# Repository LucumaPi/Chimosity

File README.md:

# Chimosity
Sobre el auto robótico con Jhonny Five.

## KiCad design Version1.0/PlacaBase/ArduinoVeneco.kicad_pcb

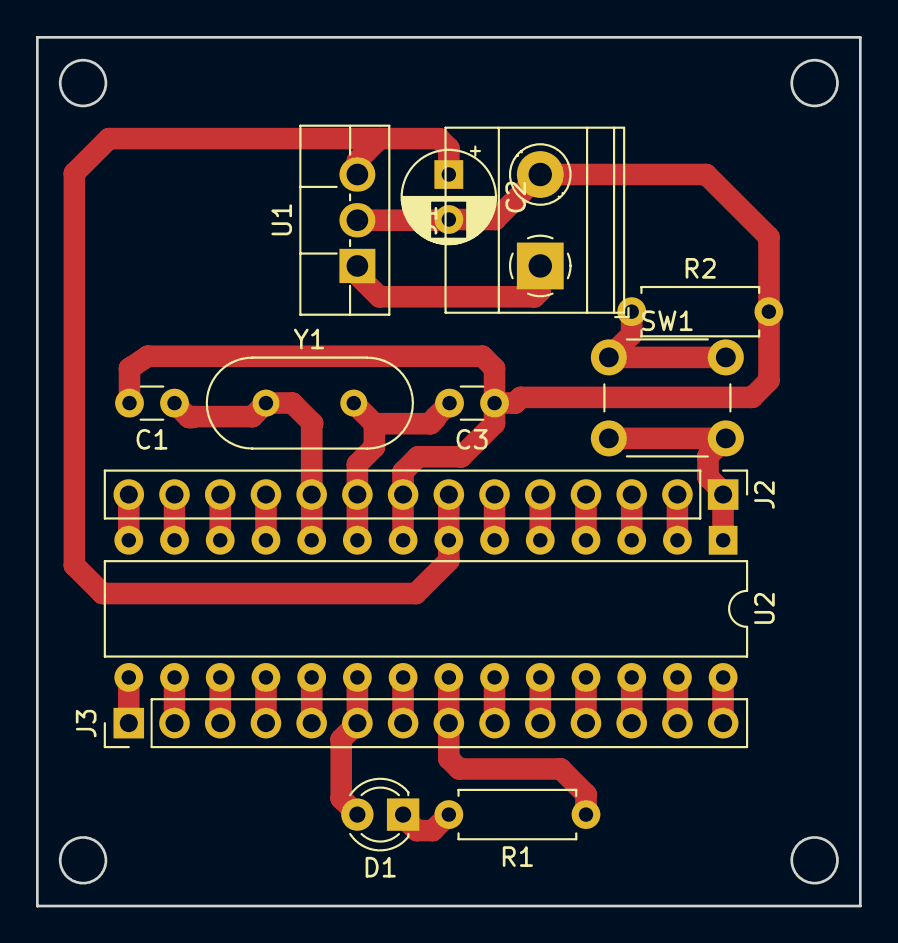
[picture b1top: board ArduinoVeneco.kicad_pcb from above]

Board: 2 copper layers, 45.7 x 48.3 mm, 13 parts (0 on the bottom side), 30 nets.

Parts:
C1, C3: C; C_Disc_D3.0mm_W1.6mm_P2.50mm
C2: CP; CP_Radial_D5.0mm_P2.50mm
D1: LED; LED_D3.0mm
J1: Screw_Terminal_01x02; TerminalBlock_Phoenix_MKDS-1,5-2-5.08_1x02_P5.08mm_Horizont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
J2, J3: Conn_01x14_Female; PinHeader_1x14_P2.54mm_Vertical
R1: 220; R_Axial_DIN0207_L6.3mm_D2.5mm_P7.62mm_Horizontal
R2: 10K; R_Axial_DIN0207_L6.3mm_D2.5mm_P7.62mm_Horizontal
SW1: SW_Push; SW_PUSH_6mm_H5mm
U1: L7805; TO-220F-3_Vertical
U2: ATmega328-PU; DIP-28_W7.62mm
Y1: Crystal; Crystal_HC49-4H_Vertical

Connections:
/A0: J3.9, U2.23
/A1: J3.10, U2.24
/A2: J3.11, U2.25
/A3: J3.12, U2.26
/A4: J3.13, U2.27
/A5: J3.14, U2.28
/AREF: J3.7, U2.21
/AVCC: D1.2, J3.6, U2.20
/D2: J2.4, U2.4
/D4: J2.6, U2.6
/D7: J2.13, U2.13
/D8: J2.14, U2.14
/D12: J3.4, U2.18
/D13: J3.5, U2.19
/GND: C1.2, C2.2, C3.1, J1.2, J2.8, J3.8, R1.1, R2.2, U1.2, U2.8, U2.22
/IN: J1.1, U1.1
/OSC1: C3.2, J2.9, U2.9, Y1.2
/OSC2: C1.1, J2.10, U2.10, Y1.1
/PWM3: J2.5, U2.5
/PWM5: J2.11, U2.11
/PWM6: J2.12, U2.12
/PWM9: J3.1, U2.15
/PWM10: J3.2, U2.16
/PWM11: J3.3, U2.17
/RESET: J2.1, SW1.2, U2.1
/RX-D0: J2.2, U2.2
/TX-D1: J2.3, U2.3
/VCC: C2.1, J2.7, U1.3, U2.7
unnamed: D1.1, R1.2
unnamed: R2.1, SW1.1

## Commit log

2019-10-12 Create PlacaBase
2019-10-12 Primera Version de placa Base
2019-10-13 Archivos minimos necesarios
2019-10-13 Agregando el gitignore
2019-11-09 chismosity
